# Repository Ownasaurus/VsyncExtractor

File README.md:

# VsyncExtractor
Designed to detect and output a simple vsync signal out of various video signals

Currently a work in progress; actively developing for  DVI/HDMI video protocol at the moment

Synthesizes using `prjtrellis (yosys + nextpnr for EPC5)` for use on an `LFE5UM5G-85F-EVN`

Modify `Makefile` to contain the path to your trellis install

`make` to build

`make flash` for flashing the firmware onto the SPI flash for permanant memory

`make test` for flashing the bitstream in volatile memory

Requires `openFPGALoader` for flashing

Supports TAS playback using the same serial protocol as the [TAStm32](https://github.com/Ownasaurus/TAStm32)
Also supports controller passthrough

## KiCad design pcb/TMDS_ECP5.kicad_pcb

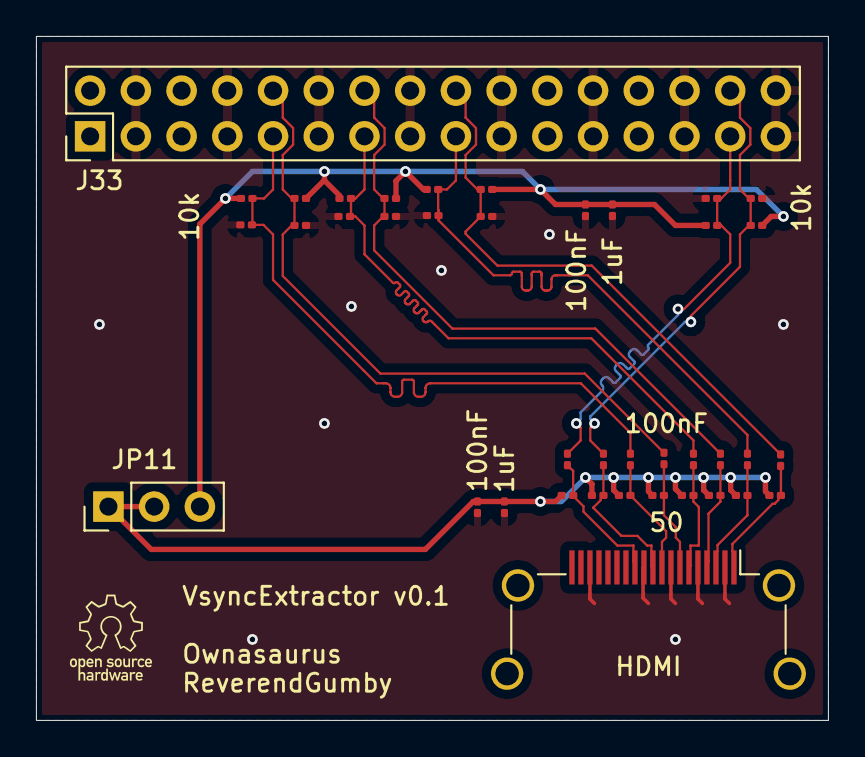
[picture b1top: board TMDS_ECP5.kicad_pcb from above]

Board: 4 copper layers, 44.0 x 38.0 mm, 39 parts (0 on the bottom side), 19 nets.

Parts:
1uF: 1u; C_0201_0603Metric
10k: 10k; R_0201_0603Metric
50: 50; R_0201_0603Metric
100nF, 100nF#2: 100n; C_0201_0603Metric
C1, C2, C3, C4, C5, C6, C7: 100n; C_0201_0603Metric
C11: 100nF; C_0201_0603Metric
C12: 1uF; C_0201_0603Metric
HDMI: HDMI_A_1.4; HDMI_A_Amphenol_10029449-x01xLF_Horizontal
J33: Conn_02x16_Odd_Even; PinHeader_2x16_P2.54mm_Vertical
JP11: Conn_01x03; PinHeader_1x03_P2.54mm_Vertical
R1, R2, R3, R5, R6, R7, R8, R9, R10, R11, R12, R13, R14, R15, R16: 10k; R_0201_0603Metric
R18, R19, R20, R21, R22, R23, R24: 50; R_0201_0603Metric

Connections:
+2V5: 1uF.2, 100nF#2.2, JP11.3, R1.1, R3.1, R5.1, R7.1, R9.1, R11.1, R13.1, R15.1
+3V3: 50.2, C11.2, C12.2, JP11.1, JP11.2, R18.2, R19.2, R20.2, R21.2, R22.2, R23.2, R24.2
/clk_1v25_N: C1.2, J33.29, R1.2, R2.1
/clk_1v25_P: 10k.1, C2.2, J33.30, R3.2
/clk_3v3_N: 50.1, C1.1, HDMI.12 (CK-)
/clk_3v3_P: C2.1, HDMI.10 (CK+), R18.1
/d0_1v25_N: C3.2, J33.9, R5.2, R6.1
/d0_1v25_P: C4.2, J33.10, R7.2, R8.1
/d0_3v3_N: C3.1, HDMI.9 (D0-), R19.1
/d0_3v3_P: C4.1, HDMI.7 (D0+), R20.1
/d1_1v25_N: C5.2, J33.13, R9.2, R10.1
/d1_1v25_P: C6.2, J33.14, R11.2, R12.1
/d1_3v3_N: C5.1, HDMI.6 (D1-), R21.1
/d1_3v3_P: C6.1, HDMI.4 (D1+), R22.1
/d2_1v25_N: C7.2, J33.17, R13.2, R14.1
/d2_1v25_P: 100nF.2, J33.18, R15.2, R16.1
/d2_3v3_N: C7.1, HDMI.3 (D2-), R23.1
/d2_3v3_P: 100nF.1, HDMI.1 (D2+), R24.1
GND: 1uF.1, 10k.2, 100nF#2.1, C11.1, C12.1, HDMI.2 (D2S), HDMI.5 (D1S), HDMI.8 (D0S), HDMI.11 (CKS), HDMI.17 (GND), J33.3, J33.4, J33.7, J33.8, J33.11, J33.12, J33.15, J33.16, J33.19, J33.20, J33.23, J33.24, J33.27, J33.28, J33.31, J33.32, R2.2, R6.2, R8.2, R10.2, R12.2, R14.2, R16.2

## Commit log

2024-05-06 initial commit; wip
2024-05-10 initial pcb commit
2024-05-10 revised pcb layout
2024-05-10 minor cleanup
2024-05-11 length matching
2024-05-11 silk screen cleanup
2024-05-12 clean silkscren; trace repair; DRC pass
